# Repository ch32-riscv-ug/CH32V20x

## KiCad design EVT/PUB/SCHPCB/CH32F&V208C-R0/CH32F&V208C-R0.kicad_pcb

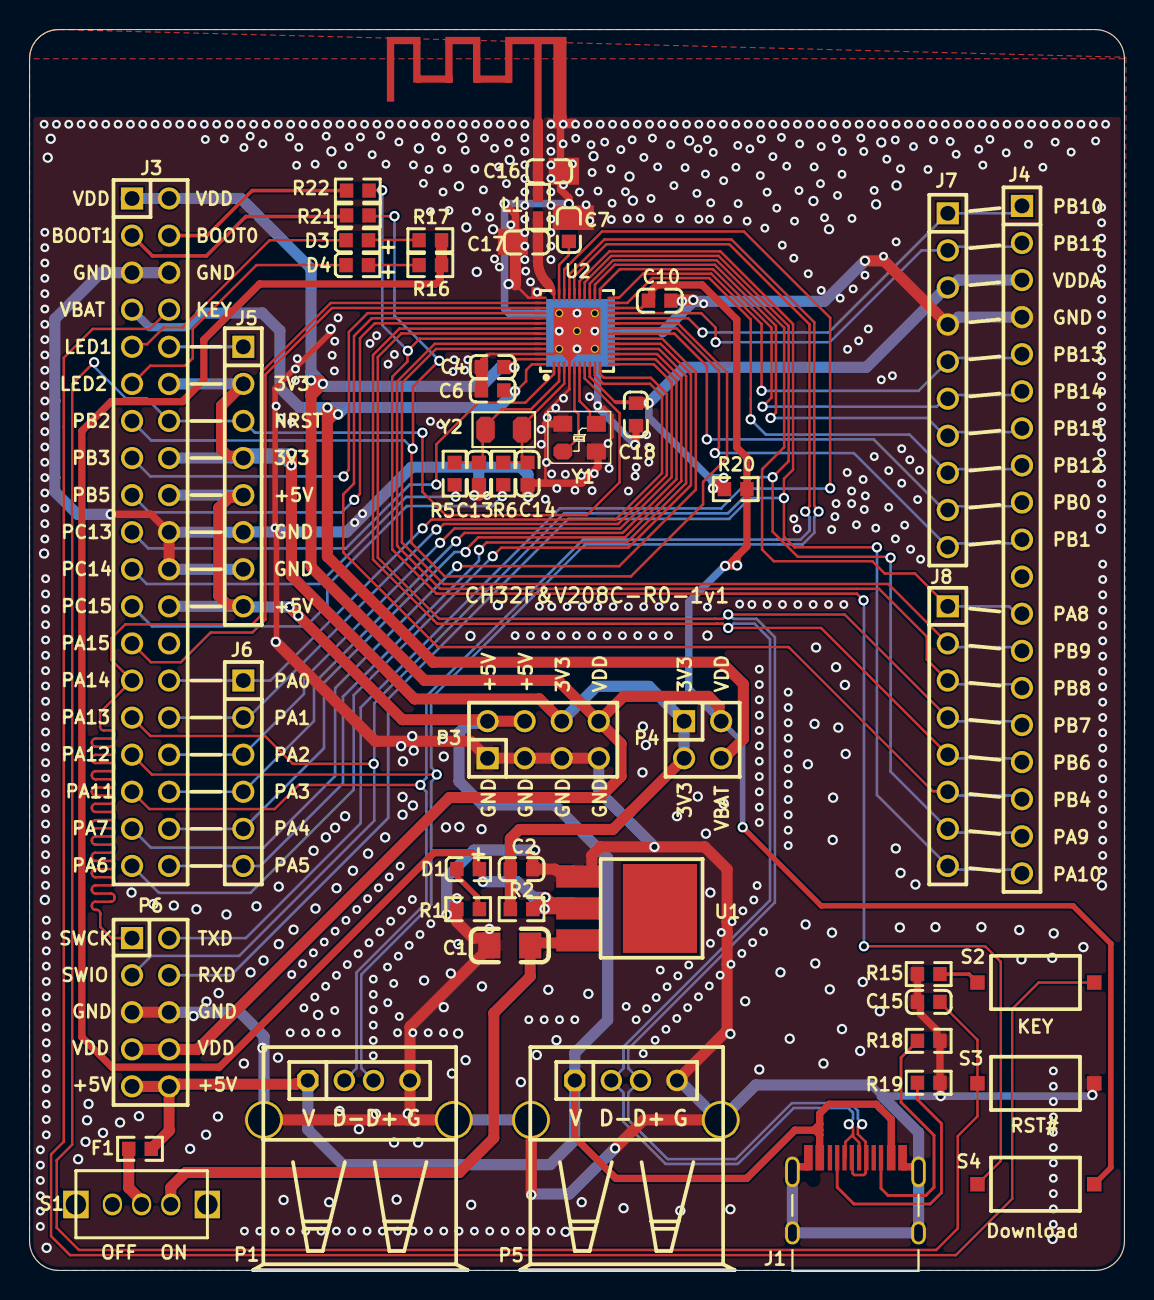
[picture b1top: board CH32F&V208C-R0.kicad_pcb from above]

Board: 2 copper layers, 75.0 x 85.0 mm, 50 parts (0 on the bottom side), 65 nets.

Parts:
C1: 10uF; 3216_C
C2: 10uF; 0603_C
C4, C6, C10, C15, C18: 0.1uF; 0603_C
C7: 1uF; 0603_C
C13, C14: 12pF; 0603_C
C16, C17: 1.8pF; 0603_C
D1: power; 0603+
D3, D4: RED; 0603+
E1: ANTENNA; ANT-F-1-2.4G-1.6mmFR4
F1: 500mA; 0603
J1: TYPE-C-Receptacle-2.0
J3: HEADER 19x2; IDC38-2.54MM
J4: Header 19; SIP19-2.54mm
J5, J8: Header 8; SIP8-2.54mm
J6: Header 6; SIP6-2.54MM
J7: Header 10; SIP10-2.54mm
L1: 1.8nH; 0603
P1, P5: USB; USBAF
P3: HEADER 4x2; IDC8-2.54mm
P4: Header 2X2; IDC4-2.54mm
P6: LINK; IDC10-2.54mm
R1, R16, R17: 1K; 0603
R2, R20: 0Ω; 0603
R5, R6: NC(0R); 0603
R15, R21, R22: 10K; 0603
R18, R19: NC(5.1K); 0603
S1: SW SPDT; SW1
S2: KEY; SMD_6.1x3.65x2.5mm-KEY
S3: RST#; SMD_6.1x3.65x2.5mm-KEY
S4: Download; SMD_6.1x3.65x2.5mm-KEY
U1: 1117-3.3V; SOT-223
U2: CH32V208C; QFN48_5x5
Y1: 32MHz; XT3225
Y2: 32768Hz; FC-135

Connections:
3V3: C2.1, J3.12, J3.16, J5.2, J5.4, P3.6, P4.1, P4.3, R2.1
3V3S: D1.1, R2.2, R16.1, R17.1, U1.2
+5V: F1.1, J1.A4, J1.B4, J3.18, J3.24, J5.5, J5.8, P1.1, P3.2, P3.4, P5.1, P6.9, P6.10
ANT: C17.2, L1.1, U2.34
BOOT0: R22.2, S4.2, U2.43
BOOT1: J3.13, R21.1, U2.19
CC1: J1.A5, R19.1
CC2: J1.B5, R18.1
GND: C1.2, C2.2, C4.2, C6.2, C7.2, C10.1, C13.1, C14.1, C15.1, C16.1, C17.1, C18.2, E1.0, J1.0, J1.A1, J1.B1, J3.5, J3.6, J3.20, J3.22, J4.4, J5.6, J5.7, J7.4, P1.0, P1.4, P3.1, P3.3, P3.5, P3.7, P5.0, P5.4, P6.5, P6.6, R1.1, R15.1, R18.2, R19.2, S3.1, U1.1, U2.0, U2.4, U2.35, U2.46, Y1.2, Y1.4
KEY: J3.8, S2.1
LED1: D3.2, J3.9
LED2: D4.2, J3.11
NRST: C15.2, J3.14, J5.3, S3.2, U2.7
NetC16_2: C16.2, E1.1, L1.2
NetD1_2: D1.2, R1.2
NetD3_1: D3.1, R17.2
NetD4_1: D4.1, R16.2
NetF1_2: F1.2, S1.1
NetJ3_3: J3.3, R21.2
NetJ3_4: J3.4, R22.1
NetJ3_10: J3.10, J5.1
NetR15_2: R15.2, S2.2
PA0: J3.28, J6.1, U2.9
PA1: J3.30, J6.2, U2.10
PA2: J3.32, J6.3, U2.11
PA3: J3.34, J6.4, U2.12
PA4: J3.36, J6.5, U2.13
PA5: J3.38, J6.6, U2.14
PA6: J3.37, U2.15
PA7: J3.35, U2.16
PA8: J4.12, J8.1, U2.27
PA9: J4.18, J8.7, P6.2, U2.28
PA10: J4.19, J8.8, P6.4, U2.29
PA11: J3.33, P1.2, U2.30
PA12: J3.31, P1.3, U2.31
PA13: J3.29, P6.3, U2.32
PA14: J3.27, P6.1, U2.36
PA15: J3.25, U2.37
PB0: J4.9, J7.9, U2.17
PB1: J4.10, J7.10, U2.18
PB3: J3.15, U2.38
PB4: J4.17, J8.6, U2.39
PB5: J3.17, U2.40
PB6: J1.A7, J1.B7, J4.16, J8.5, P5.2, U2.41
PB7: J1.A6, J1.B6, J4.15, J8.4, P5.3, U2.42
PB8: J4.14, J8.3, U2.44
PB9: J4.13, J8.2, U2.45
PB10: J4.1, J7.1, U2.20
PB11: J4.2, J7.2, U2.21
PB12: J4.8, J7.8, U2.23
PB13: J4.5, J7.5, U2.24
PB14: J4.6, J7.6, U2.25
PB15: J4.7, J7.7, U2.26
PC13: J3.19, U2.1
PC14: J3.21, R5.1
PC15: J3.23, R6.1
V5V: C1.1, S1.2, U1.3
VBAT: C6.1, J3.7, P4.4, U2.48
VDD: C4.1, C10.2, J3.1, J3.2, P3.8, P4.2, P6.7, P6.8, R20.1, S4.1, U2.22, U2.47
VDDA: C18.1, J4.3, J7.3, R20.2, U2.8
VINTA: C7.1, U2.33
X32IN: C13.2, R5.2, U2.2, Y2.1
X32OUT: C14.2, R6.2, U2.3, Y2.2
XIN: U2.5, Y1.1
XOUT: U2.6, Y1.3

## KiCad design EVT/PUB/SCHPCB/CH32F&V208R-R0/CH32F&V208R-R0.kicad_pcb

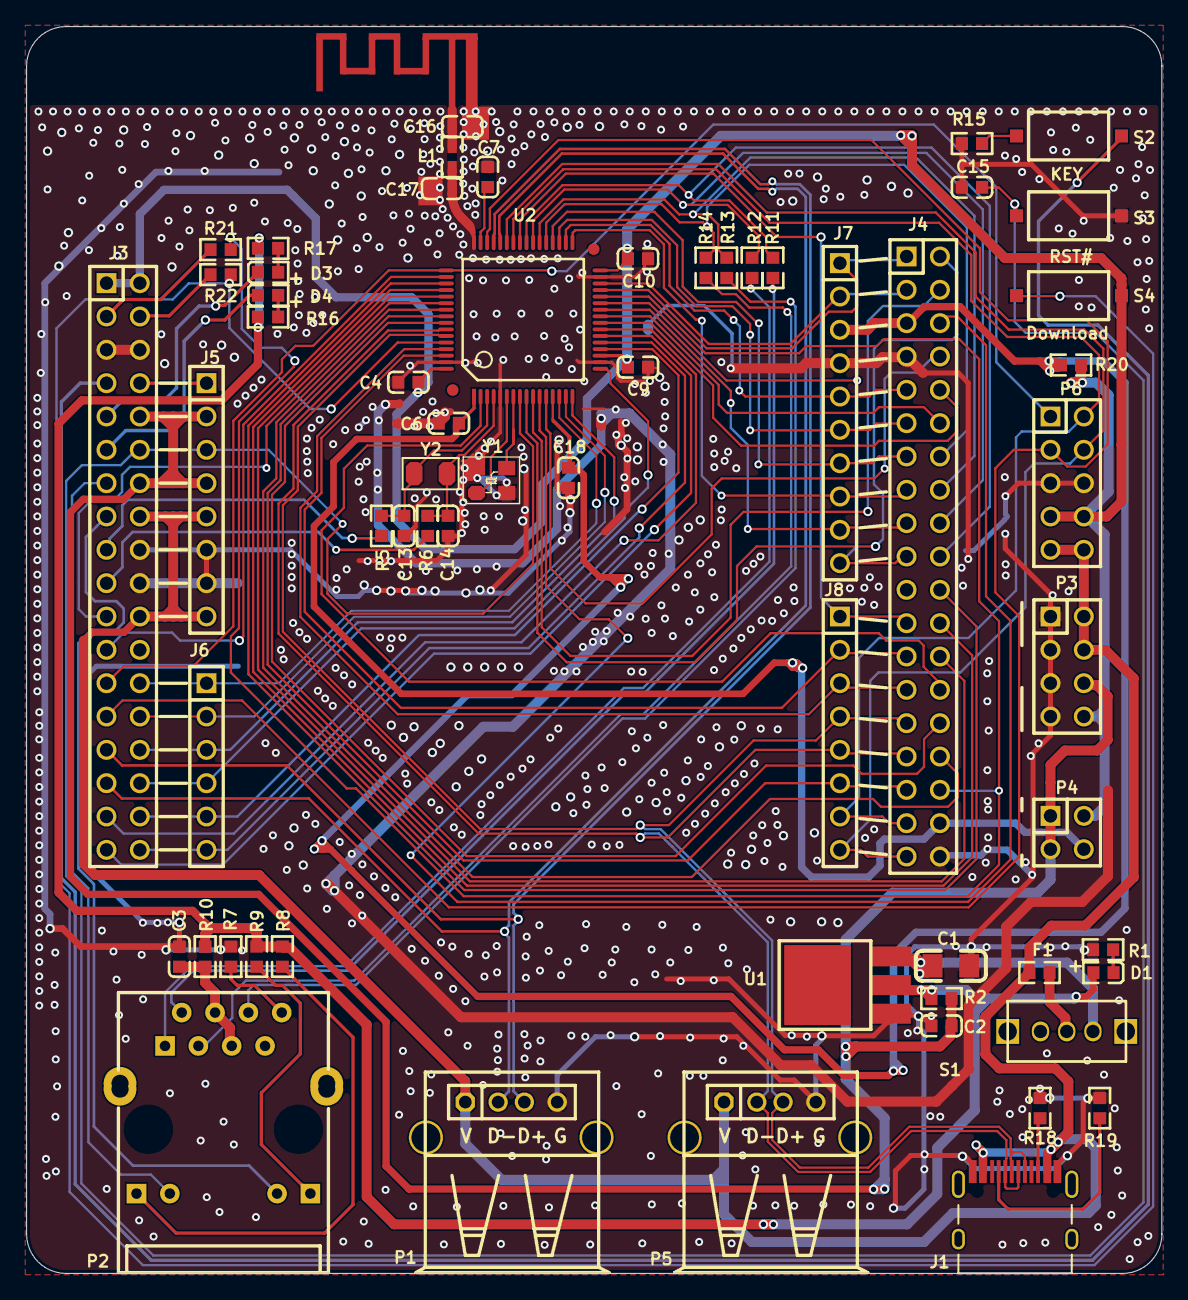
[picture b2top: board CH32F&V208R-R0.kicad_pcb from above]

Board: 2 copper layers, 86.5 x 95.0 mm, 61 parts (0 on the bottom side), 89 nets.

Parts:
C1: 10uF; 3216_C
C2: 10uF; 0603_C
C3, C7: 1uF; 0603_C
C4, C6, C9, C10, C15, C18: 0.1uF; 0603_C
C13, C14: 12pF; 0603_C
C16, C17: 1.8pF; 0603_C
D1: power; 0603+
D3, D4: RED; 0603+
E1: ANTENNA; ANT-F-1-2.4G-1.6mmFR4
F1: 500mA; 0603
J1: TYPE-C-Receptacle-2.0
J3: Header 18X2; IDC36-2.54mm
J4: Header 19X2; IDC38-2.54mm
J5, J8: Header 8; SIP8-2.54mm
J6: Header 6; SIP6-2.54MM
J7: Header 10; SIP10-2.54mm
L1: 1.8nH; 0603
P1, P5: USB; USBAF
P2: HR911105A
P3: HEADER 4x2; IDC8-2.54mm
P4: Header 2X2; IDC4-2.54mm
P6: LINK; IDC10-2.54mm
R1, R8, R9, R16, R17: 1K; 0603
R2, R7, R10, R11, R12, R13, R14, R20: 0Ω; 0603
R5, R6: NC(0R); 0603
R15, R21, R22: 10K; 0603
R18, R19: NC(5.1K); 0603
S1: SW SPDT; SW1
S2: KEY; SMD_6.1x3.65x2.5mm-KEY
S3: RST#; SMD_6.1x3.65x2.5mm-KEY
S4: Download; SMD_6.1x3.65x2.5mm-KEY
U1: 1117-3.3V; SOT-223
U2: CH32V208R; LQFP64M_10x10
Y1: 32MHz; XT3225
Y2: 32768Hz; FC-135

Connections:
3V3: C2.1, J3.10, J3.14, J5.2, J5.4, P3.6, P4.1, P4.3, R2.1
3V3S: D1.1, R2.2, R8.1, R9.1, R10.2, R16.1, R17.1, U1.2
+5V: F1.1, J1.A4, J1.B4, J3.16, J3.22, J5.5, J5.8, P1.1, P3.2, P3.4, P5.1, P6.9, P6.10
ANT: C17.2, L1.1, U2.48
BOOT0: R22.2, S4.2, U2.60
BOOT1: J4.34, R21.1, U2.28
CC1: J1.A5, R19.1
CC2: J1.B5, R18.1
ELED1: J3.13, P2.10
ELED2: J3.15, P2.11
ERXN: P2.6, R13.2
ERXP: P2.3, R14.2
ETXN: P2.2, R11.2
ETXP: P2.1, R12.2
GND: C1.2, C2.2, C3.1, C4.2, C6.2, C7.2, C9.1, C10.1, C13.1, C14.1, C15.1, C16.1, C17.1, C18.2, E1.0, J1.A1, J1.B1, J3.5, J3.6, J3.18, J3.20, J4.7, J4.38, J5.6, J5.7, J7.4, P1.4, P3.1, P3.3, P3.5, P3.7, P5.4, P6.5, P6.6, R1.1, R7.1, R15.1, R18.2, R19.2, S3.1, U1.1, U2.5, U2.18, U2.31, U2.63, Y1.2, Y1.4
KEY: J3.7, S2.1
LED1: D3.2, J3.9
LED2: D4.2, J3.11
NRST: C15.2, J3.12, J5.3, S3.2, U2.8
NetC3_2: C3.2, P2.4, P2.5, R10.1
NetC16_2: C16.2, E1.1, L1.2
NetD1_2: D1.2, R1.2
NetD3_1: D3.1, R17.2
NetD4_1: D4.1, R16.2
NetF1_2: F1.2, S1.1
NetJ3_3: J3.3, R21.2
NetJ3_4: J3.4, R22.1
NetJ3_8: J3.8, J5.1
NetP2_8: P2.8, R7.2
NetP2_9: P2.9, R8.2
NetP2_12: P2.12, R9.2
NetR15_2: R15.2, S2.2
PA0: J3.26, J6.1, U2.14
PA1: J3.28, J6.2, U2.15
PA2: J3.30, J6.3, U2.16
PA3: J3.32, J6.4, U2.17
PA4: J3.34, J6.5, U2.20
PA5: J3.36, J6.6, U2.21
PA6: J3.35, U2.22
PA7: J3.33, U2.23
PA8: J4.23, J8.1, U2.41
PA9: J4.35, J8.7, P6.2, U2.42
PA10: J4.37, J8.8, P6.4, U2.43
PA11: J3.31, P1.2, U2.44
PA12: J3.29, P1.3, U2.45
PA13: J3.27, P6.3, U2.46
PA14: J3.25, P6.1, U2.49
PA15: J3.23, U2.50
PB0: J4.17, J7.9, U2.26
PB1: J4.19, J7.10, U2.27
PB3: J4.32, U2.55
PB4: J4.33, J8.6, U2.56
PB5: J4.30, U2.57
PB6: J1.A7, J1.B7, J4.31, J8.5, P5.2, U2.58
PB7: J1.A6, J1.B6, J4.29, J8.4, P5.3, U2.59
PB8: J4.27, J8.3, U2.61
PB9: J4.25, J8.2, U2.62
PB10: J4.1, J7.1, U2.29
PB11: J4.3, J7.2, U2.30
PB12: J4.15, J7.8, U2.33
PB13: J4.9, J7.5, U2.34
PB14: J4.11, J7.6, U2.35
PB15: J4.13, J7.7, U2.36
PC0: J4.2, U2.9
PC1: J4.4, U2.10
PC2: J4.6, U2.11
PC3: J4.8, U2.12
PC4: J4.10, U2.24
PC5: J4.12, U2.25
PC6: J4.14, R14.1, U2.37
PC7: J4.16, R13.1, U2.38
PC8: J4.18, R12.1, U2.39
PC9: J4.20, R11.1, U2.40
PC10: J4.22, U2.51
PC11: J4.24, U2.52
PC12: J4.26, U2.53
PC13: J4.28, U2.2
PC14: J3.17, R5.1
PC15: J3.19, R6.1
PD2: J3.21, U2.54
V5V: C1.1, S1.2, U1.3
VBAT: C6.1, J4.36, P4.4, U2.1
VDD: C4.1, C9.2, C10.2, J3.1, J3.2, P3.8, P4.2, P6.7, P6.8, R20.1, S4.1, U2.19, U2.32, U2.64
VDDA: C18.1, J4.5, J7.3, R20.2, U2.13
VINTA: C7.1, U2.47
X32IN: C13.2, R5.2, U2.3, Y2.1
X32OUT: C14.2, R6.2, U2.4, Y2.2
XIN: U2.6, Y1.1
XOUT: U2.7, Y1.3

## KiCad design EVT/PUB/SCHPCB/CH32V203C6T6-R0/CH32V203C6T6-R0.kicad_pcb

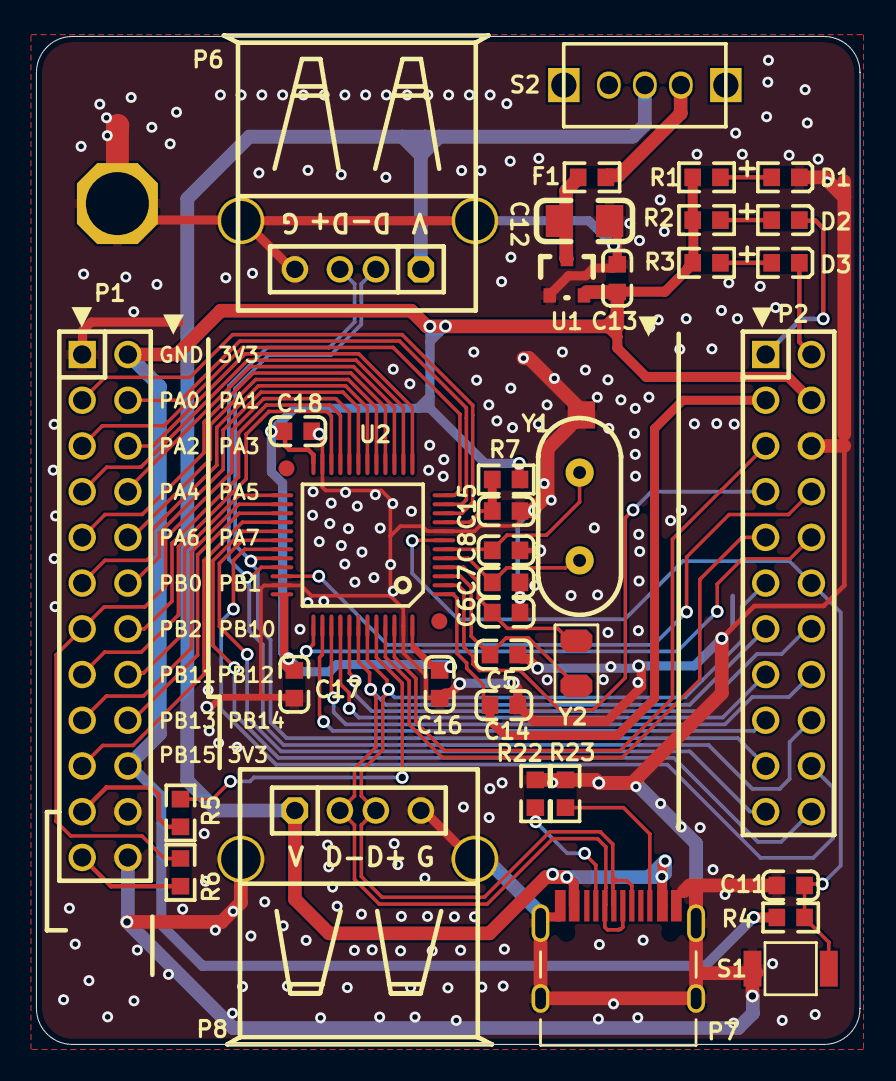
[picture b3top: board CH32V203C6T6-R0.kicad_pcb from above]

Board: 2 copper layers, 45.8 x 56.0 mm, 36 parts (0 on the bottom side), 55 nets.

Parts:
C5, C6: 12pF; 0603_C
C7, C8: 22pF; 0603_C
C11, C14, C15, C16, C17, C18: 0.1uF; 0603_C
C12: 10uF; 3216_C
C13: 2.2uF; 0603_C
D1: POWER red; 0603+
D2: LED1; 0603+
D3: LED2; 0603+
F1: 500mA; 0603
P1: HEADER 12x2; IDC24-2.54MM
P2: HEADER 11x2; IDC22-2.54MM
P6, P8: USB_A; USBAF
P7: TYPE-C; TYPE-C-Receptacle-2.0
R1, R2, R3: 1K; 0603
R4, R5, R6: 10K; 0603
R7: 0Ω; 0603
R22, R23: NC(5.1K); 0603
S1: KEY; 贴片按键
S2: SW; KEY2
U1: 6219P33M; SOT-23
U2: CH32V203CxT; LQFP48
Y1: 8M; XT_AT49
Y2: 32.768k; FC-135

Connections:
+5V: P6.1, P7.A4, P7.B4, P8.1, S2.1
BOOT0: R5.1, U2.44
BOOT1: P1.13, R6.1, U2.20
GND: C5.2, C6.2, C7.1, C8.1, C11.1, C12.2, C13.2, C14.2, C15.2, C16.1, C17.1, C18.1, D1.2, P1.1, P1.22, P1.24, P2.6, P6.0, P6.4, P7.0, P7.A1, P7.B1, P8.0, P8.4, R22.2, R23.2, S1.2, U1.1, U2.8, U2.23, U2.35, U2.47, Y1.0
LED1: D2.2, P2.1
LED2: D3.2, P2.2
NRST: C11.2, P2.12, R4.1, S1.1, U2.7
NetD1_1: D1.1, R1.1
NetD2_1: D2.1, R2.2
NetD3_1: D3.1, R3.2
NetF1_1: F1.1, S2.3
NetP1_21: P1.21, R5.2
NetP1_23: P1.23, R6.2
NetP7_A5: P7.A5, R22.1
NetP7_B5: P7.B5, R23.1
PA0: P1.3, U2.10
PA1: P1.4, U2.11
PA2: P1.5, U2.12
PA3: P1.6, U2.13
PA4: P1.7, U2.14
PA5: P1.8, U2.15
PA6: P1.9, U2.16
PA7: P1.10, U2.17
PA8: P2.22, U2.29
PA9: P2.21, U2.30
PA10: P2.20, U2.31
PA11: P2.19, P6.2, U2.32
PA12: P2.18, P6.3, U2.33
PA13: P2.8, U2.34
PA14: P2.10, U2.37
PA15: P2.17, U2.38
PB0: P1.11, U2.18
PB1: P1.12, U2.19
PB3: P2.16, U2.39
PB4: P2.15, U2.40
PB5: P2.14, U2.41
PB6: P2.13, P7.A7, P7.B7, P8.2, U2.42
PB7: P2.11, P7.A6, P7.B6, P8.3, U2.43
PB8: P2.9, U2.45
PB9: P2.5, U2.46
PB10: P1.14, U2.21
PB11: P1.15, U2.22
PB12: P1.16, U2.25
PB13: P1.17, U2.26
PB14: P1.18, U2.27
PB15: P1.19, U2.28
PC13: P2.7, U2.2
PC14: C5.1, U2.3, Y2.1
PC15: C6.1, U2.4, Y2.2
PD0: C7.2, U2.5, Y1.2
PD1: C8.2, U2.6, Y1.1
V5V: C12.1, F1.2, U1.3
VBAT: C14.1, P2.3, U2.1
VCC: C13.1, C16.2, C17.2, C18.2, P1.2, P1.20, P2.4, R1.2, R2.1, R3.1, R4.2, R7.1, U1.2, U2.24, U2.36, U2.48
VDDA: C15.1, R7.2, U2.9

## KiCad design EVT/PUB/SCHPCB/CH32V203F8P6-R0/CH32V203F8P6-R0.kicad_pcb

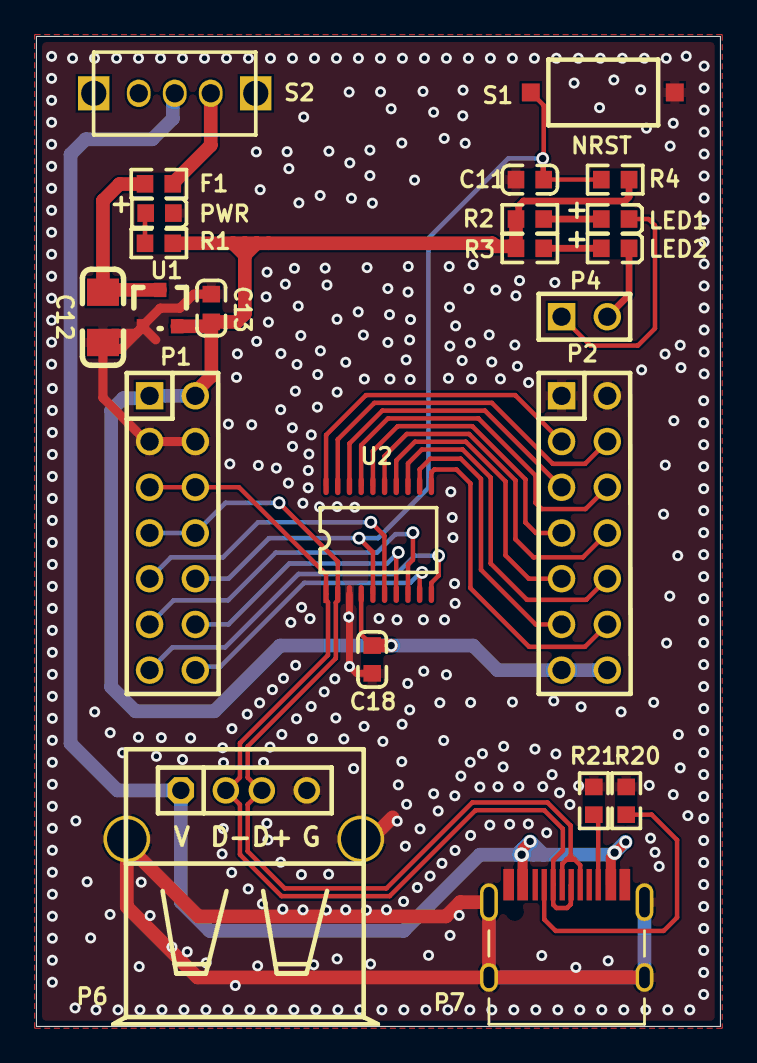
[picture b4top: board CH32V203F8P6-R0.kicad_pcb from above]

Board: 2 copper layers, 38.0 x 55.0 mm, 23 parts (0 on the bottom side), 30 nets.

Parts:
C11, C18: 0.1uF; 0603_C
C12: 10uF; 3216_C
C13: 2.2uF; 0603_C
F1: 500mA; 0603
LED1: LED1; 0603+
LED2: LED2; 0603+
P1, P2: Header 7X2; IDC14-2.54mm
P4: 2HEAD; SIP2-2.54mm
P6: USB_A; USBAF
P7: TYPE-C; TYPE-C-Receptacle-2.0
PWR: POWER red; 0603+
R1, R2, R3: 1K; 0603
R4: 10K; 0603
R20, R21: NC(5.1K); 0603
S1: NRST; SMD_6.1x3.65x2.5mm-KEY
S2: SW; KEY2
U1: 6219P33M; SOT-23
U2: CH32V203F8; TSSOP20

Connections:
+5V: P6.1, P7.A4, P7.B4, S2.1
GND: C11.1, C12.2, C13.1, C18.1, P1.3, P1.4, P2.1, P2.2, P6.0, P6.4, P7.0, P7.A1, P7.B1, PWR.2, R20.2, R21.2, S1.2, U1.1, U2.3
LED1: LED1.2, P4.1
LED2: LED2.2, P4.2
NRST: C11.2, P1.10, R4.1, S1.1, U2.5
NetC12_1: C12.1, F1.2, U1.3
NetF1_1: F1.1, S2.3
NetLED1_1: LED1.1, R2.2
NetLED2_1: LED2.1, R3.2
NetP7_A5: P7.A5, R20.1
NetP7_B5: P7.B5, R21.1
NetPWR_1: PWR.1, R1.1
PA0: P1.9, U2.6
PA1: P1.12, U2.7
PA2: P1.11, U2.8
PA3: P1.14, U2.9
PA4: P2.12, U2.11
PA5: P2.11, U2.12
PA6: P1.13, U2.10
PA7: P2.10, U2.13
PA8: P2.5, U2.18
PA9: P2.4, U2.19
PA10: P2.3, U2.20
PA13: P1.5, P1.6, P6.2, P7.A7, P7.B7, U2.1
PA14: P1.7, P1.8, P6.3, P7.A6, P7.B6, U2.2
PB0: P2.9, U2.14
PB13: P2.8, U2.15
PB14: P2.7, U2.16
PB15: P2.6, U2.17
VCC: C13.2, C18.2, P1.1, P1.2, P2.13, P2.14, R1.2, R2.1, R3.1, R4.2, U1.2, U2.4

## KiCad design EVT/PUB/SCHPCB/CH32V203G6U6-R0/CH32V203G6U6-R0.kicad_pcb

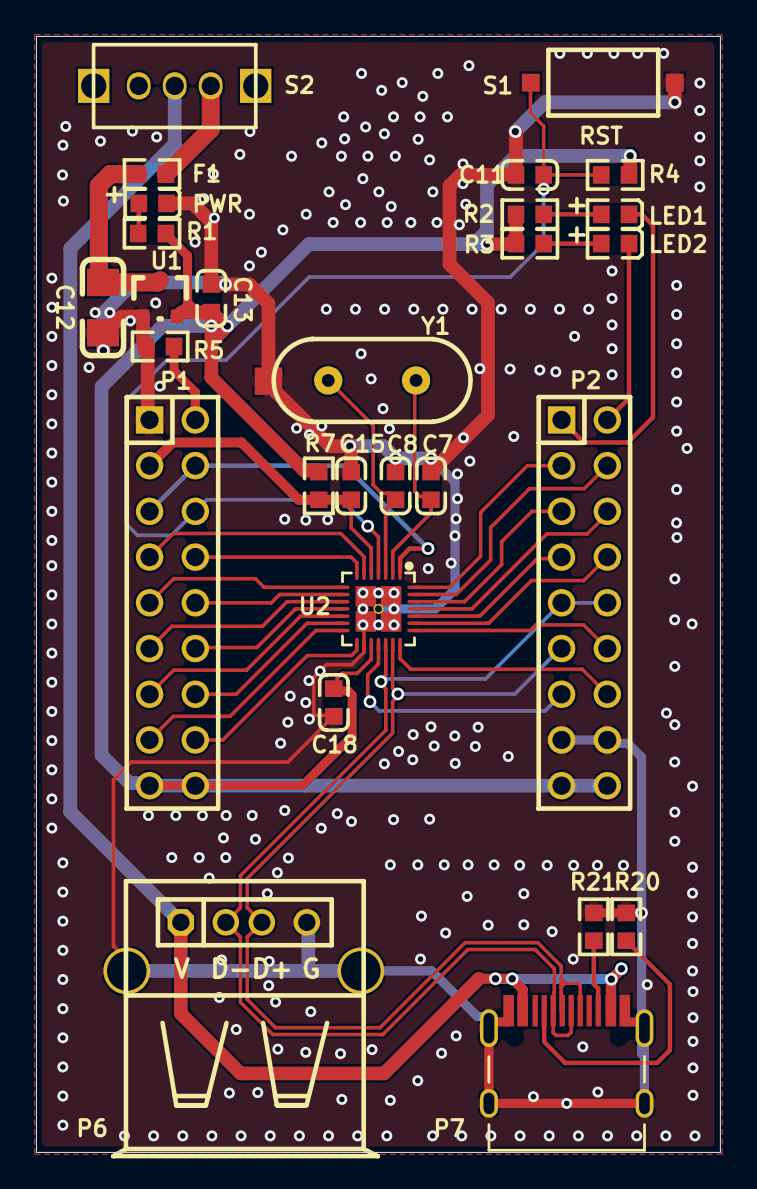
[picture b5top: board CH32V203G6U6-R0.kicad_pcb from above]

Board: 2 copper layers, 38.0 x 62.0 mm, 28 parts (0 on the bottom side), 39 nets.

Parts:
C7, C8: 22pF; 0603_C
C11, C15, C18: 0.1uF; 0603_C
C12: 10uF; 3216_C
C13: 2.2uF; 0603_C
F1: 500mA; 0603
LED1: LED1 blue; 0603+
LED2: LED2 blue; 0603+
P1, P2: HEADER 9x2; IDC18-2.54MM
P6: USB_A; USBAF
P7: TYPE-C; TYPE-C-Receptacle-2.0
PWR: POWER red; 0603+
R1, R2, R3: 1K; 0603
R4: NC(10K); 0603
R5: 4.7K; 0603
R7: 0Ω; 0603
R20, R21: NC(5.1K); 0603
S1: RST; SMD_6.1x3.65x2.5mm-KEY
S2: SW; KEY2
U1: 6219P33M; SOT-23
U2: CH32V203G6U; QFN28_4x4
Y1: 8M; XT_AT49

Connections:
+5V: P6.1, P7.A4, P7.B4, S2.1
BOOT0: P1.4, P1.5, U2.1
GND: C7.1, C8.1, C11.1, C12.2, C13.1, C15.2, C18.1, P1.1, P2.15, P2.16, P6.0, P6.4, P7.0, P7.A1, P7.B1, PWR.2, R5.2, R20.2, R21.2, S1.2, U1.1, U2.0, U2.16, Y1.0
LED1: LED1.2, P2.1
LED2: LED2.2, P2.2
NRST: C11.2, P1.6, R4.1, S1.1, U2.4
NetC12_1: C12.1, F1.2, U1.3
NetF1_1: F1.1, S2.3
NetLED1_1: LED1.1, R2.2
NetLED2_1: LED2.1, R3.2
NetP1_2: P1.2, R5.1
NetP7_A5: P7.A5, R20.1
NetP7_B5: P7.B5, R21.1
NetPWR_1: PWR.1, R1.1
PA0: P1.7, U2.6
PA1: P1.8, U2.7
PA2: P1.9, U2.8
PA3: P1.10, U2.9
PA4: P1.11, U2.10
PA5: P1.12, U2.11
PA6: P1.13, U2.12
PA7: P1.14, U2.13
PA9: P2.13, U2.18
PA10: P2.9, P2.10, P6.2, P7.A7, P7.B7, U2.19
PA12: P2.11, P6.3, P7.A6, P7.B6, U2.20
PA13: P2.14, U2.21
PA14: P2.12, U2.22
PA15: P2.8, U2.23
PB0: P1.15, U2.14
PB1: P1.16, U2.15
PB3: P2.7, U2.24
PB4: P2.6, U2.25
PB5: P2.5, U2.26
PB6: P2.4, U2.27
PB7: P2.3, U2.28
PD0: C7.2, U2.2, Y1.2
PD1: C8.2, U2.3, Y1.1
VCC: C13.2, C18.2, P1.17, P1.18, P2.17, P2.18, R1.2, R2.1, R3.1, R4.2, R7.1, U1.2, U2.17
VDDA: C15.1, P1.3, R7.2, U2.5

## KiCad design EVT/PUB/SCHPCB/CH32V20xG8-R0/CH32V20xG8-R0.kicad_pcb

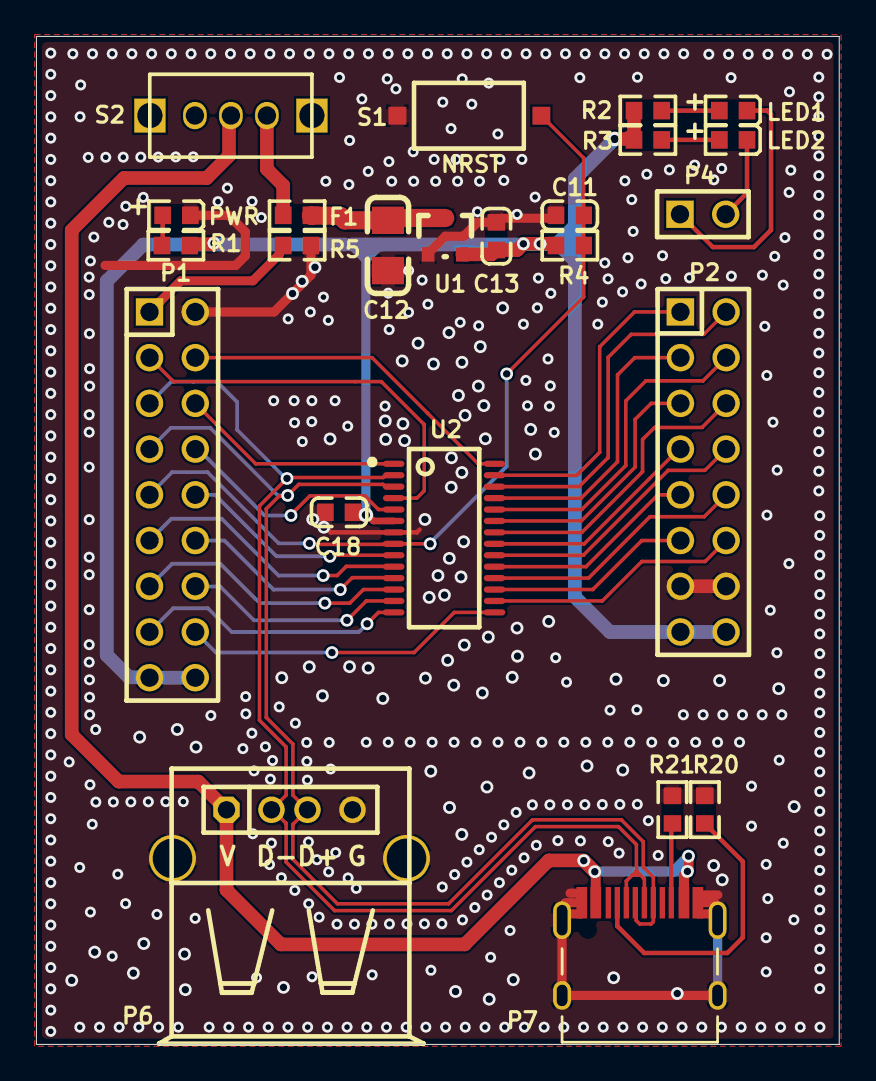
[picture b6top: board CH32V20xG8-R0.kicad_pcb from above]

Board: 2 copper layers, 44.6 x 56.0 mm, 24 parts (0 on the bottom side), 39 nets.

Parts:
C11, C18: 0.1uF; 0603_C
C12: 10uF; 3216_C
C13: 2.2uF; 0603_C
F1: 500mA; 0603
LED1: LED1 blue; 0603+
LED2: LED2 blue; 0603+
P1: HEADER 9x2; IDC18-2.54MM
P2: Header 8X2; IDC16-2.54mm
P4: 2HEAD; SIP2-2.54mm
P6: USB_A; USBAF
P7: TYPE-C; TYPE-C-Receptacle-2.0
PWR: POWER red; 0603+
R1, R2, R3: 1K; 0603
R4, R5: 10K; 0603
R20, R21: NC(5.1K); 0603
S1: NRST; SMD_6.1x3.65x2.5mm-KEY
S2: SW; KEY2
U1: 6219P33M; SOT-23
U2: CH32V203G8R; QSOP28

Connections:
+5V: P6.1, P7.A4, P7.B4, S2.1
BOOT0: P1.3, U2.4
GND: C11.1, C12.2, C13.1, C18.1, P1.2, P2.13, P2.14, P6.0, P6.4, P7.0, P7.A1, P7.B1, PWR.2, R5.1, R20.2, R21.2, S1.2, U1.1, U2.7
LED1: LED1.2, P4.1
LED2: LED2.2, P4.2
NRST: C11.2, P1.9, R4.1, S1.1, U2.8
NetC12_1: C12.1, F1.2, U1.3
NetF1_1: F1.1, S2.3
NetLED1_1: LED1.1, R2.2
NetLED2_1: LED2.1, R3.2
NetP1_1: P1.1, R5.2
NetP7_A5: P7.A5, R20.1
NetP7_B5: P7.B5, R21.1
NetPWR_1: PWR.1, R1.1
PA0: P1.10, U2.9
PA1: P1.11, U2.10
PA2: P1.12, U2.11
PA3: P1.13, U2.12
PA4: P1.16, U2.15
PA5: P2.12, U2.16
PA6: P1.14, U2.13
PA7: P2.11, U2.17
PA8: P2.4, U2.24
PA9: P2.3, U2.25
PA10: P2.2, U2.26
PA11: P2.1, U2.27
PA12: P1.4, U2.28
PA14: P1.6, U2.1
PB0: P1.15, U2.14
PB1: P2.8, U2.20
PB6: P1.5, P6.2, P7.A7, P7.B7, U2.2
PB7: P1.7, P6.3, P7.A6, P7.B6, U2.3
PB8: P1.8, U2.5
PB10: P2.10, U2.18
PB11: P2.9, U2.19
PB13: P2.7, U2.21
PB14: P2.6, U2.22
PB15: P2.5, U2.23
VCC: C13.2, C18.2, P1.17, P1.18, P2.15, P2.16, R1.2, R2.1, R3.1, R4.2, U1.2, U2.6
